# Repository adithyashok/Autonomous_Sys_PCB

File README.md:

# Undegraduate Research for the Autonomous Systems Group, Prof. Ufuk Topcu
PCB Design files for the 3DPrinting Drone Project
University of Texas, Austin

This is what I wanted to solve: 

Results:

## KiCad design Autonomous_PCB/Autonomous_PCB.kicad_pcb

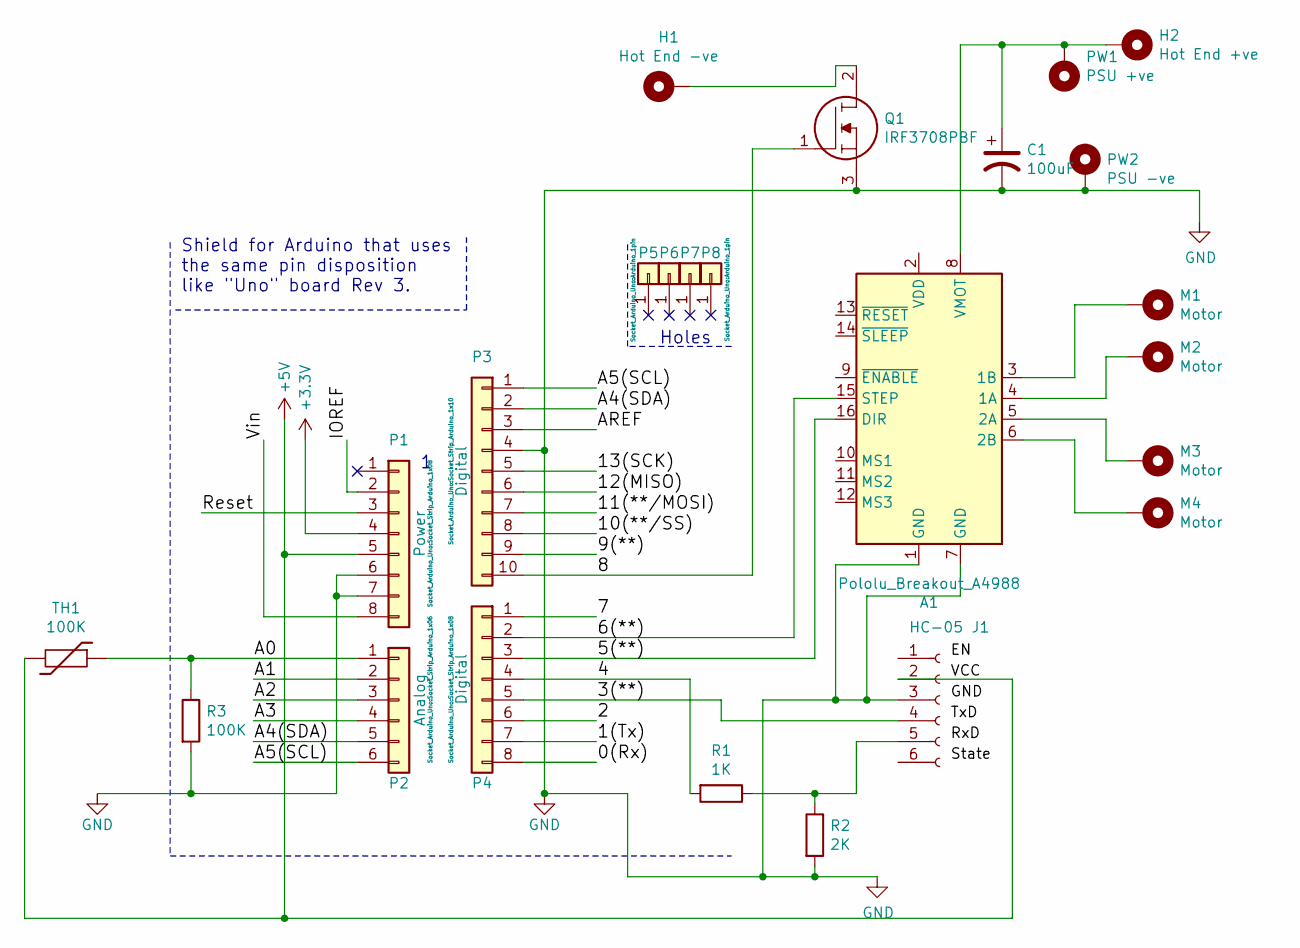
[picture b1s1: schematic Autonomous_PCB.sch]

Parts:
A1: Pololu_Breakout_A4988; Pololu_Breakout-16_15.2x20.3mm
C1: 100uF; CP_Radial_D10.0mm_P5.00mm
H1: Hot End -ve; MountingHole_2.2mm_M2_DIN965_Pad
H2: Hot End +ve; MountingHole_2.2mm_M2_DIN965_Pad
J1: HC-05; SHDR6W70P0X254_1X6_1524X244X870P
M1, M2, M3, M4: Motor; MountingHole_2.2mm_M2_DIN965_Pad
P1: Power; Socket_Strip_Arduino_1x08
P2: Analog; Socket_Strip_Arduino_1x06
P3: Digital; Socket_Strip_Arduino_1x10
P4: Digital; Socket_Strip_Arduino_1x08
P5, P6, P7, P8: CONN_01X01; Arduino_1pin
PW1: PSU +ve; MountingHole_2.2mm_M2_DIN965_Pad
PW2: PSU -ve; MountingHole_2.2mm_M2_DIN965_Pad
Q1: IRF3708PBF; TO254P469X1042X1967-3P; Mouser Part Number 942-IRF3708PBF
R1: 1K; R_Axial_DIN0207_L6.3mm_D2.5mm_P7.62mm_Horizontal
R2: 2K; R_Axial_DIN0207_L6.3mm_D2.5mm_P7.62mm_Horizontal
R3: 100K; R_Axial_DIN0207_L6.3mm_D2.5mm_P7.62mm_Horizontal
TH1: 100K; R_Axial_DIN0204_L3.6mm_D1.6mm_P5.08mm_Horizontal

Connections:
+3V3: P1.4
+5V: J1.2, P1.5, TH1.2
/0(Rx): P4.8
/1(Tx): P4.7
/2: P4.6
/3(**): J1.4, P4.5
/4: P4.4, R1.2
/5(**): A1.16 (DIR), P4.3
/6(**): A1.15 (STEP), P4.2
/7: P4.1
/8: P3.10, Q1.1
/9(**): P3.9
/10(**/SS): P3.8
/11(**/MOSI): P3.7
/12(MISO): P3.6
/13(SCK): P3.5
/A0: P2.1, R3.1, TH1.1
/A1: P2.2
/A2: P2.3
/A3: P2.4
/A4(SDA): P2.5, P3.2
/A5(SCL): P2.6, P3.1
/AREF: P3.3
/IOREF: P1.2
/Reset: P1.3
/Vin: P1.8
GND: A1.1 (GND), A1.7 (GND), C1.2, J1.3, P1.6, P1.7, P3.4, PW2.1, Q1.3, R2.2, R3.2
unnamed: A1.3 (1B), M1.1
unnamed: A1.4 (1A), M2.1
unnamed: A1.5 (2A), M3.1
unnamed: A1.6 (2B), M4.1
unnamed: A1.8 (VMOT), C1.1, H2.1, PW1.1
unnamed: H1.1, Q1.2
unnamed: J1.5, R1.1, R2.1

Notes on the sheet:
Shield for Arduino that uses the same pin disposition like "Uno" board Rev 3.
Holes

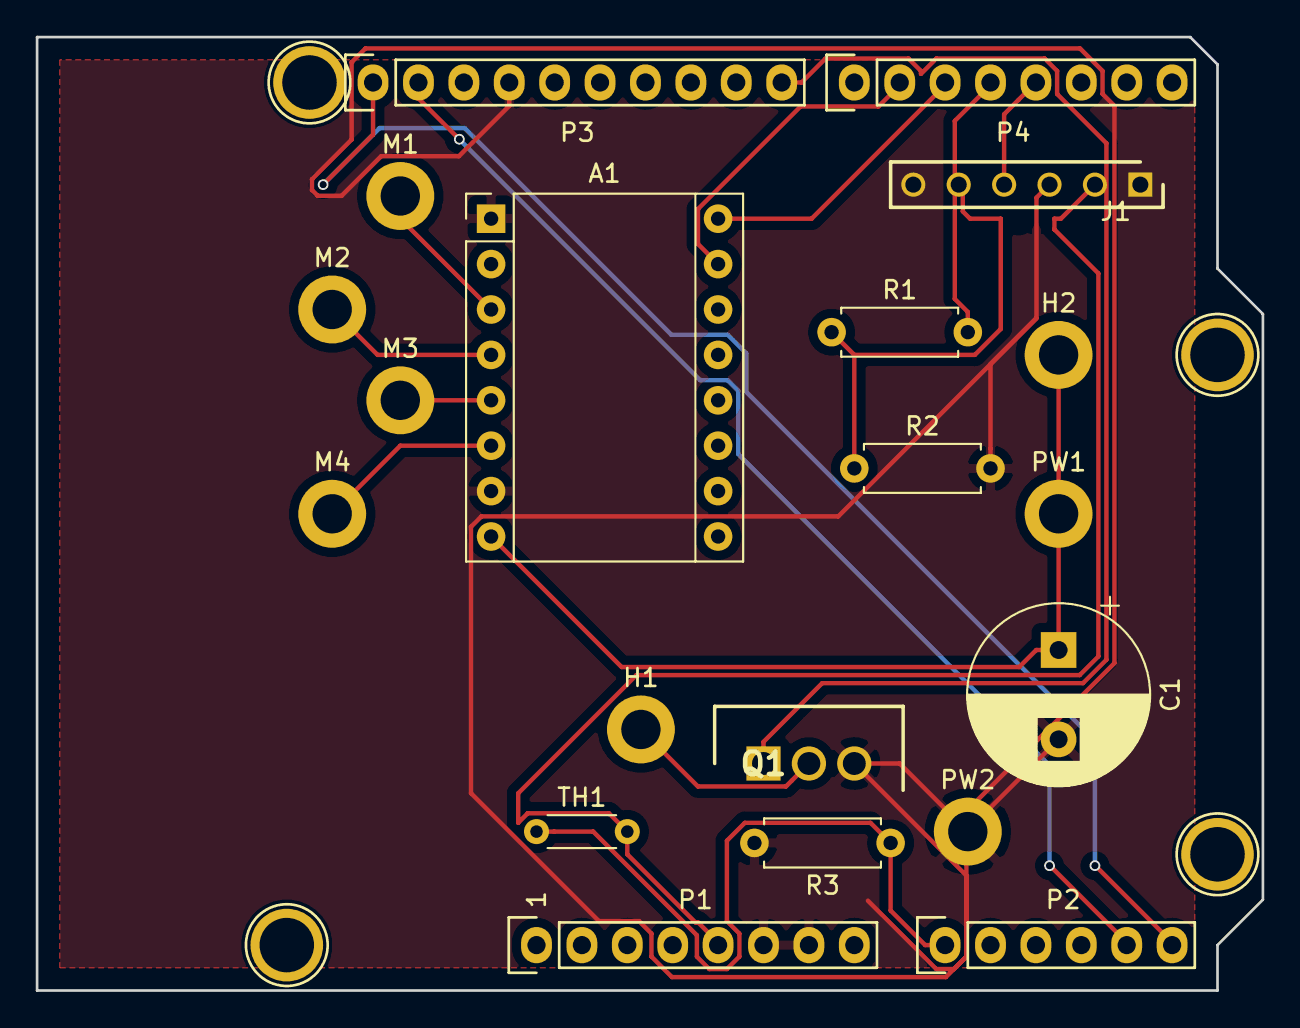
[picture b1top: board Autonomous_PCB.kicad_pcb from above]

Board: 2 copper layers, 68.6 x 53.3 mm, 24 parts (0 on the bottom side), 17 nets.
